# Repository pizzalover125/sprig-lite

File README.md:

# sprig-lite
A miniature version of the Sprig game console. Featuring the smallest, Arduino-compatible DIP processor and 3 push buttons!

## Images:

## BOM 
NOTE: I am not using AliExpress because they are super unreliable and misdelivered my old package. Fourtanetly, I found it at my neighbor's house. They also just mark it as delivered when it is out for delivery. Also tariffs. 
* 5x EG1218 Slide Switch
* 2x Attiny85 w/ Socket
* 40x 1k Resistors
* 2x i2c 0.96" OLED
* 1x Keystone 2462 Battery Holder
* 1x Arduino Uno R3 (to program the board)

$57.14 w/ tax + shipping

* 1x Foam Tape
* Misc Screws

$15.00 from Home Depot w/ tax

* 5x JLC PCB ($15.55)
* Breadboard Wires (FREE)
* 3mm LEDs (FREE)
* 6mm Buttons (FREE)

**Total: $87.69**

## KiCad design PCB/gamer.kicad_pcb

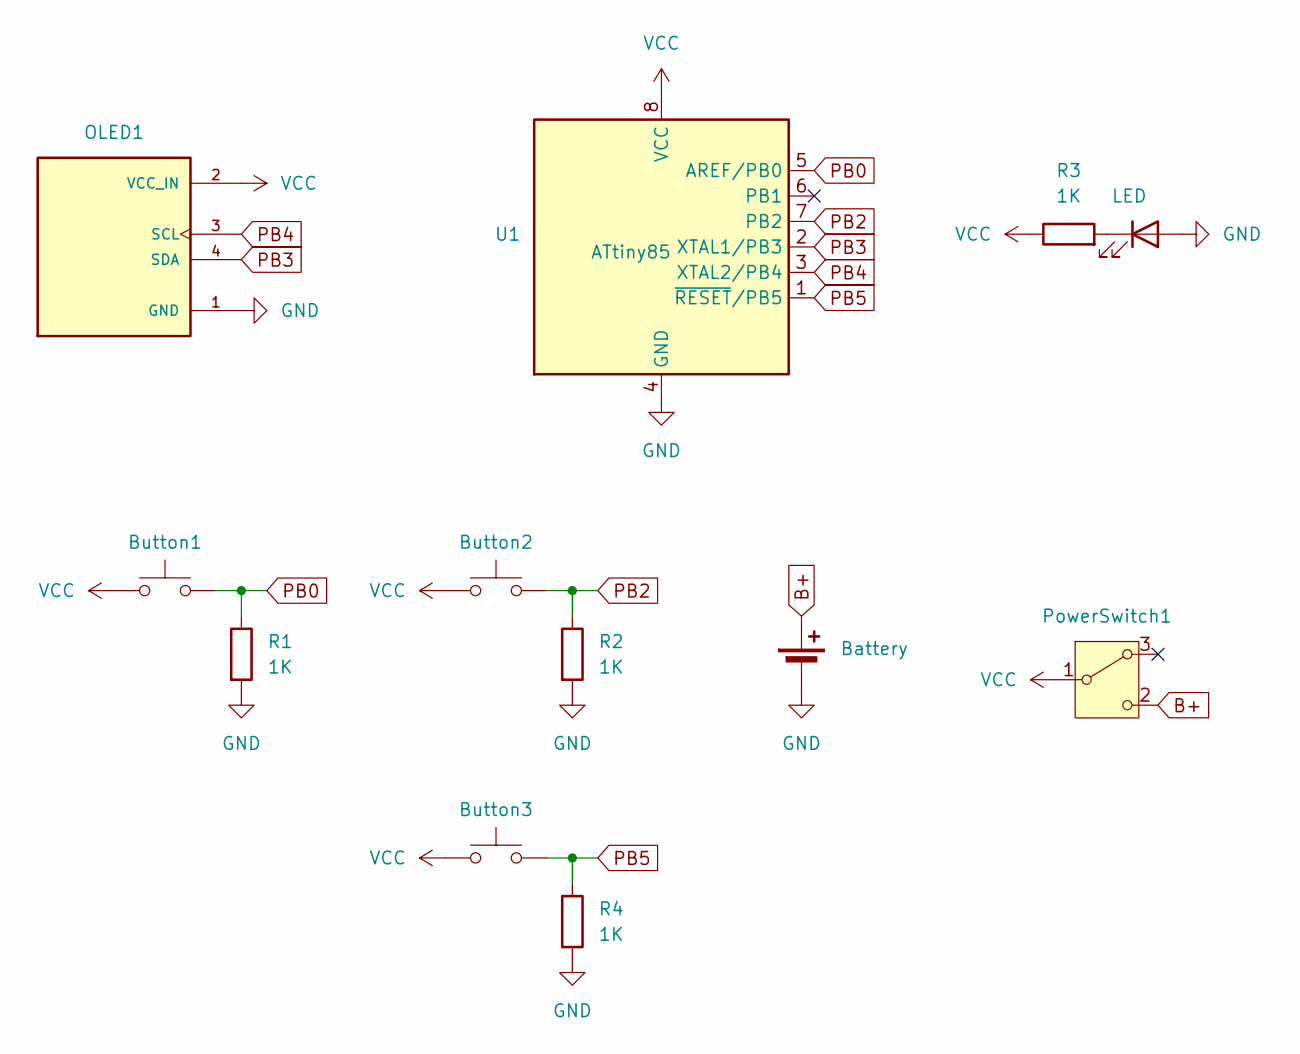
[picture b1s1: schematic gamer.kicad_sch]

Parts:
BT1: Battery; BatteryHolder_Keystone_2462_2xAA
Button1, Button2, Button3: SW_Push; SW_PUSH_6mm_H4.3mm
D1: LED; LED_D3.0mm
OLED1: DM-OLED096-636; MODULE_DM-OLED096-636; PARTREV 2018-09-10
PowerSwitch1: SW_Wuerth_450301014042; SW_EG1218
R1, R2, R3, R4: 1K; R_Axial_DIN0207_L6.3mm_D2.5mm_P7.62mm_Horizontal
U1: ATtiny85; DIP-8_W7.62mm

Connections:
B+: BT1.1 (+), PowerSwitch1.2 (C)
GND: BT1.2 (-), D1.2 (A), OLED1.1 (GND), R1.2, R2.2, R4.2, U1.4 (GND)
unnamed: D1.1 (K), R3.2
PB0: Button1.2, R1.1, U1.5 (AREF/PB0)
PB2: Button2.2, R2.1, U1.7 (PB2)
PB3: OLED1.4 (SDA), U1.2 (XTAL1/PB3)
PB4: OLED1.3 (SCL), U1.3 (XTAL2/PB4)
PB5: Button3.2, R4.1, U1.1 (~RESET/PB5)
VCC: Button1.1, Button2.1, Button3.1, OLED1.2 (VCC_IN), PowerSwitch1.1 (B), R3.1, U1.8 (VCC)

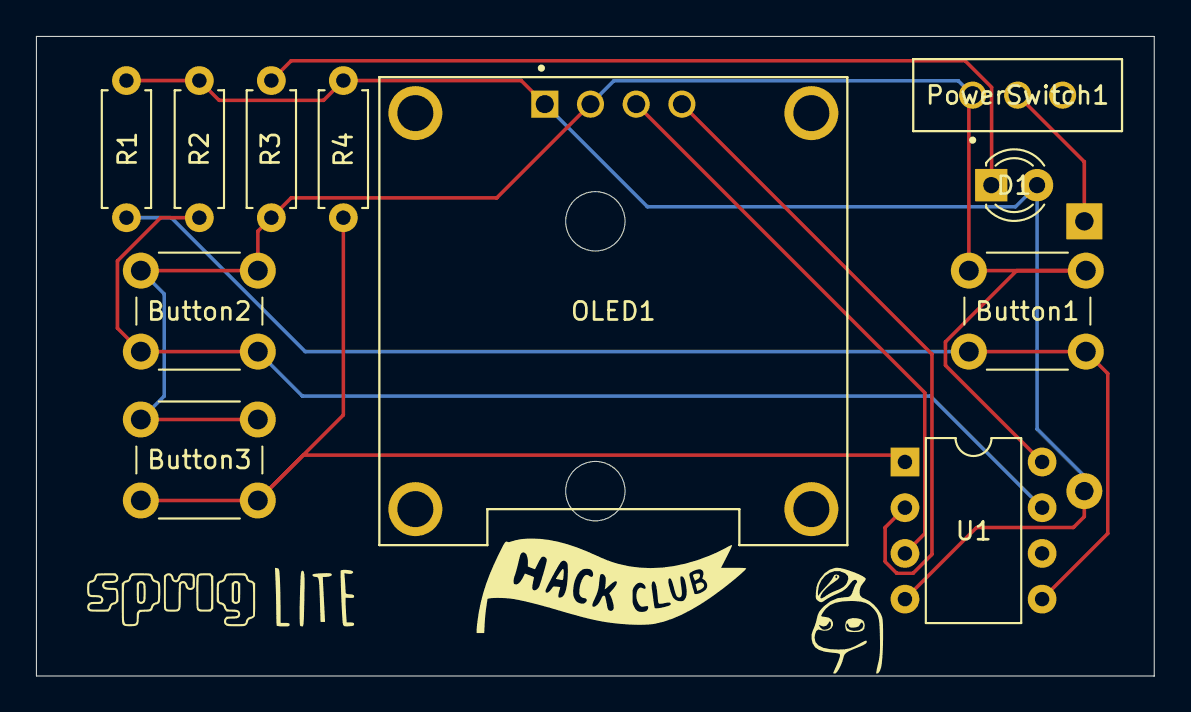
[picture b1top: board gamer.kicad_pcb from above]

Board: 2 copper layers, 62.1 x 35.5 mm, 12 parts (1 on the bottom side), 9 nets.

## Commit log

2025-06-11 added firmware and changed the overall format.
